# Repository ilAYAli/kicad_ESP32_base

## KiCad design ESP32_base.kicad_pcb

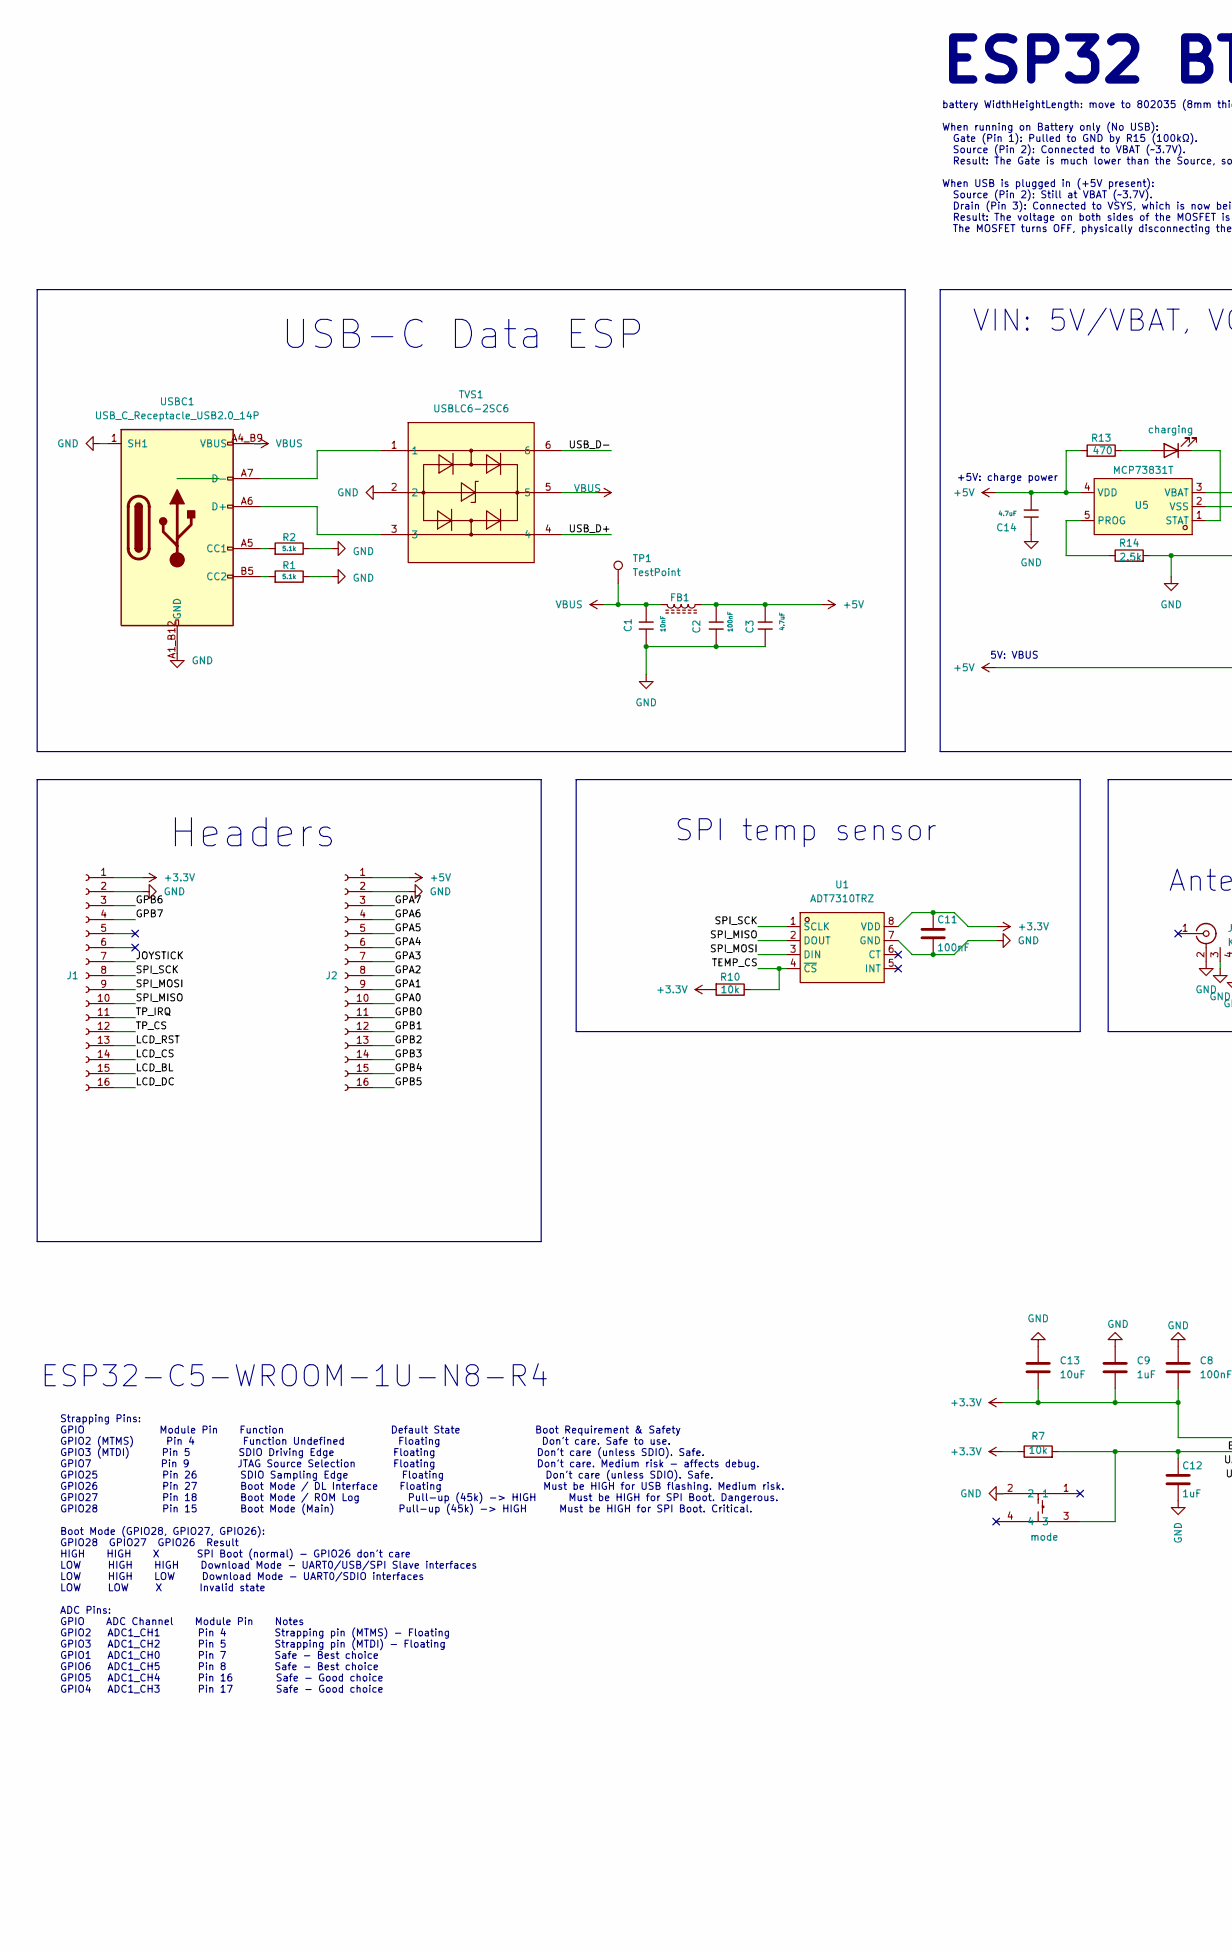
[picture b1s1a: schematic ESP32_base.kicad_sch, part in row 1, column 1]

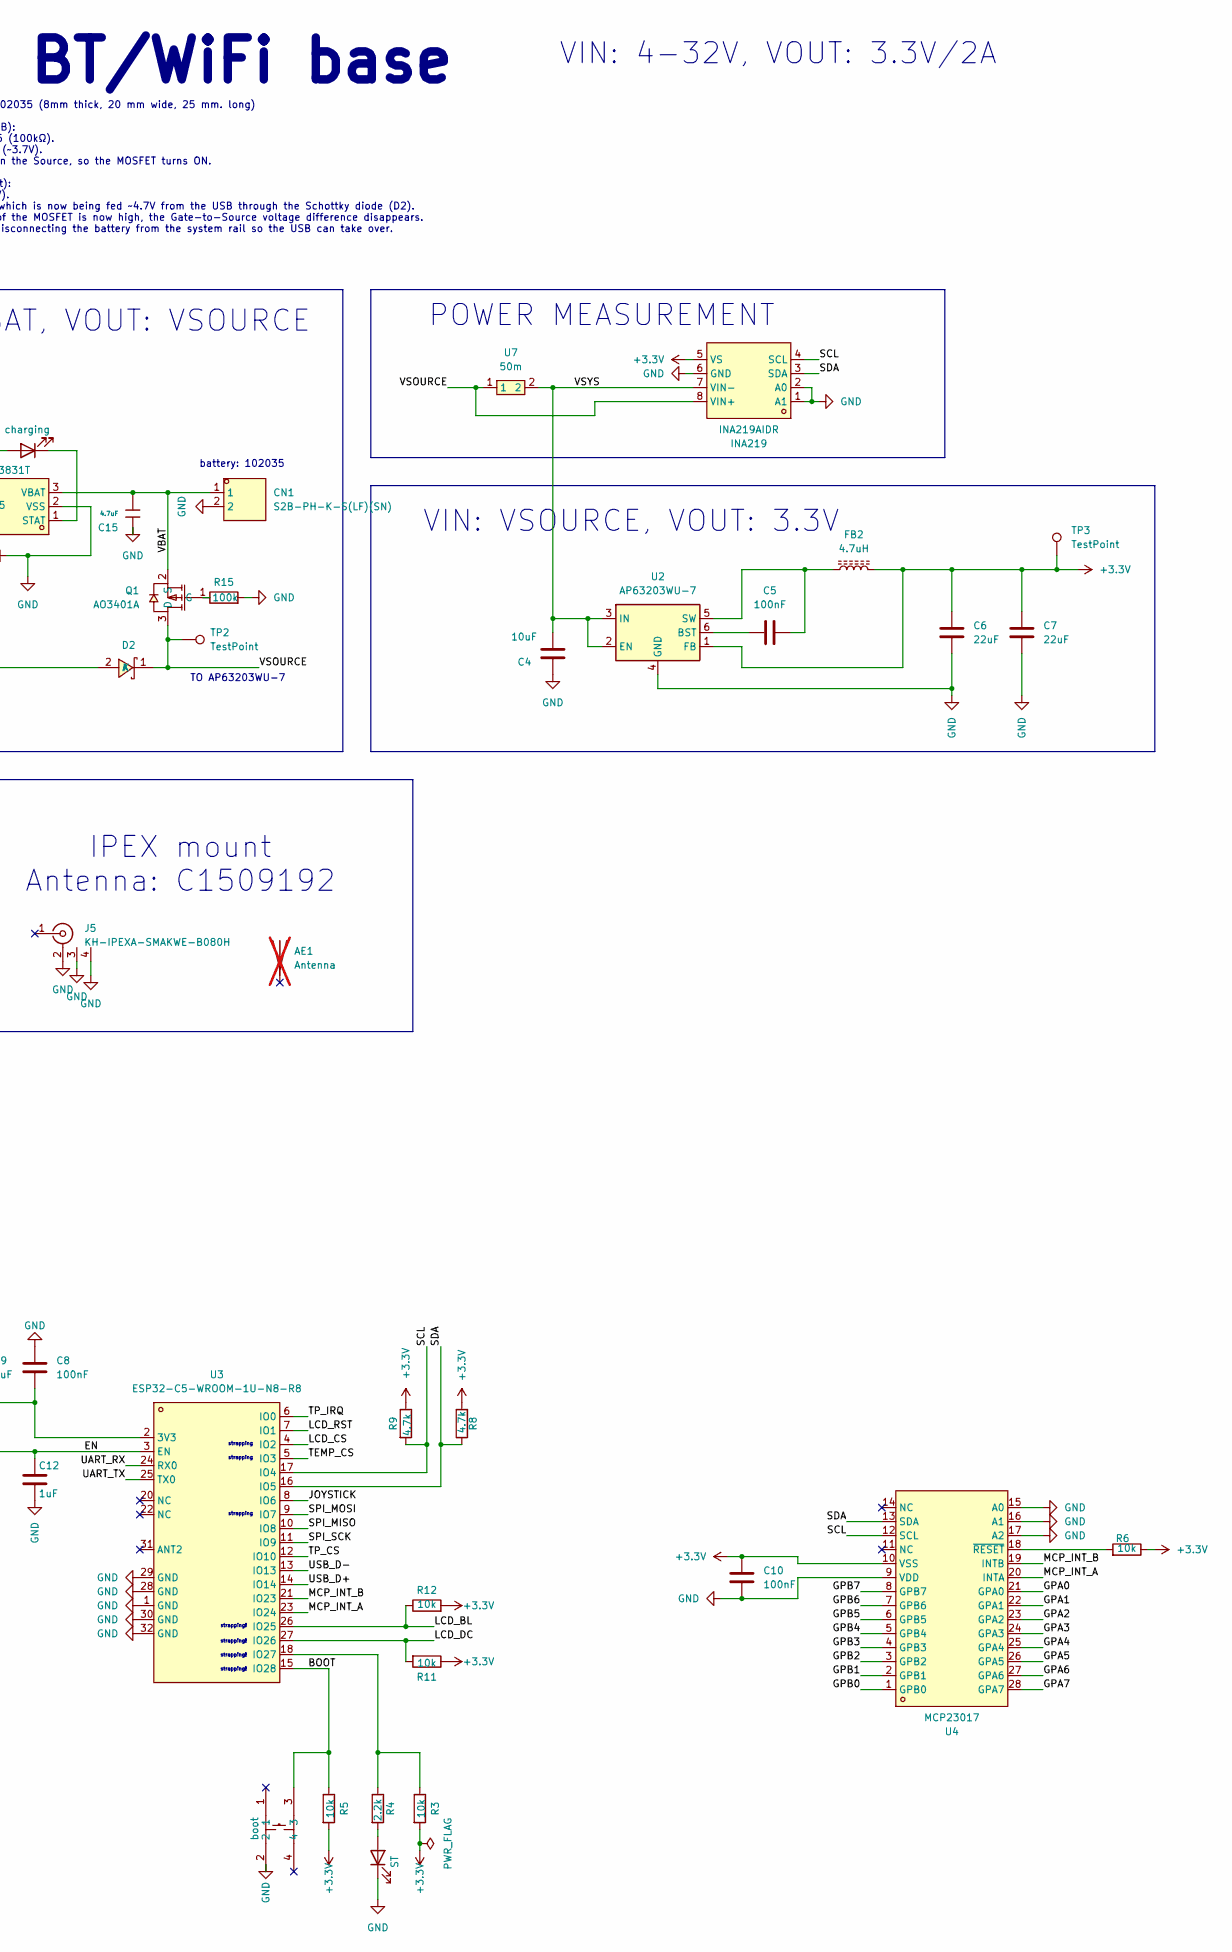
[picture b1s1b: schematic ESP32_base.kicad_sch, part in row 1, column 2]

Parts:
AE1: Antenna; LCSC Part C1509192; not fitted
C1: 10nF; C_0805_2012Metric; Mfr. Part CC0805KRX7R9BB103; LCSC Part C83170
C2, C5, C8, C10, C11: 100nF; C_0805_2012Metric; Mfr. Part CC0805KRX7R9BB104; LCSC Part C49678
C3: 4.7uF; C_0805_2012Metric; Mfr. Part GRM21BZ71H475KE15L; LCSC Part C437557
C4, C13: 10uF; C_0805_2012Metric; Mfr. Part GRM21BR61H106KE43L; LCSC Part C440198
C6, C7: 22uF; C_0805_2012Metric; Mfr. Part CGA0805X5R226M350MT; LCSC Part C6119901
C9, C12: 1uF; C_0805_2012Metric; Mfr. Part CL21B105KBFNNNE; LCSC Part C28323
C14, C15: 4.7uF; C_0805_2012Metric; Voltage Rated 25V; Tolerance ±10%; Part CL21A475KAQNNNE; LCSC C1779
CN1: S2B-PH-K-S(LF)(SN); CONN-TH_S2B-PH-K-S-LF-SN; LCSC Part C173752
D2: C426863; D_SOD-323; Mfr. Part PMEG1020EA,115; LCSC Part C146335
FB1: 600; L_0805_2012Metric; Mfr. Part MPZ2012S601AT000; LCSC Part C21519
FB2: 4.7uH; C_1210_3225Metric; Mfr. Part SRP3212A-4R7M
INA219: INA219AIDR; SOIC-8_L4.9-W3.9-P1.27-LS6.0-BL; LCSC Part C138706
J1: Conn_01x16_Socket; PinSocket_1x16_P2.54mm_Vertical; Mfr. Part KH-2.54FH-1X16P-H8.5; LCSC Part C19190305
J2: Conn_01x16_Socket; PinSocket_1x16_P2.54mm_Vertical; Mfr. Part KH-2.54FH-1X16P-H8.5; LCSC Part C2905421
J5: KH-IPEXA-SMAKWE-B080H; CONN-TH_KH-IPEX-SMAKWE; Mfr. Part KH-IPEXA-SMAKWE-B080H; LCSC Part C2919724
LED1: ST; LED_0805_2012Metric; Mfr. Part NCD0805G1; LCSC Part C84260
LED2: charging; LED_0805_2012Metric
Q1: AO3401A; SOT-23; LCSC Part C15127
R1, R2: 5.1k; R_0805_2012Metric; Mfr. Part 0805W8F5101T5E; LCSC Part C27834
R3, R5, R6, R7, R11, R12: 10k; R_0805_2012Metric; Mfr. Part RC0805FR-0710KL; LCSC Part C84376
R4: 2.2k; R_0805_2012Metric; Mfr. Part 0805W8F2201T5E; LCSC Part C17520
R8, R9: 4.7k; R_0805_2012Metric
R10: 10k; R_0805_2012Metric
R13: 470; R_0805_2012Metric
R14: 2.5k; R_0805_2012Metric
R15: 100k; R_0805_2012Metric
SW1: boot; SW-SMD_4P-L6.0-W6.0-P4.50-LS9.0-2; Mfr. Part TS-1002S-04526C; LCSC Part C455109
SW2: mode; SW-SMD_4P-L6.0-W6.0-P4.50-LS9.0-2; Mfr. Part TS-1002S-04526C; LCSC Part C455109
TP1, TP2, TP3: TestPoint; TestPoint_Pad_D1.0mm
TVS1: USBLC6-2SC6; SOT-23-6; Mfr. Part USBLC6-2SC6; LCSC Part C7519
U1: ADT7310TRZ; SOIC-8_L4.9-W3.9-P1.27-LS6.0-BL; Mfr. Part ADT7310TRZ; LCSC Part C660039
U2: AP63203WU-7; TSOT-23-6; Mfr. Part AP63203WU-7; LCSC Part C780769
U3: ESP32-C5-WROOM-1U-N8-R8; COMM-SMD_32P-L21.2-W18.0_ESP32-C5-WROOM-1U; Mfr. Part ESP32-C5-WROOM-1U-N8R4; LCSC Part C49308183
U4: MCP23017; SOIC-28_L18.0-W7.5-P1.27-LS10.3-BL; LCSC Part C47023
U5: MCP73831T; SOT-23-5_L3.0-W1.7-P0.95-LS2.8-BL; LCSC Part C424093
U7: 50m; R1206; Mfr. Part FRM121WFR050TM; LCSC Part C7467249
USBC1: USB_C_Receptacle_USB2.0_14P; USB-C_Receptacle

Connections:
+3.3V: C6.2, C7.2, C8.2, C9.2, C10.1, C11.1, C13.1, FB2.2, INA219.5 (VS), J1.1, R3.2, R5.2, R6.1, R7.1, R8.2, R9.1, R10.2, R11.1, R12.2, TP3.1, U1.8 (VDD), U2.1 (FB), U3.2 (3V3), U4.10 (VSS)
+5V: C2.1, C3.1, C14.1, D2.2 (A), FB1.1, J2.1, R13.2, U5.4 (VDD)
/BOOT: R5.1, SW1.3, U3.15 (IO28)
/EN: C12.1, R7.2, SW2.3, U3.3 (EN)
/GPA0: J2.10, U4.21 (GPA0)
/GPA1: J2.9, U4.22 (GPA1)
/GPA2: J2.8, U4.23 (GPA2)
/GPA3: J2.7, U4.24 (GPA3)
/GPA4: J2.6, U4.25 (GPA4)
/GPA5: J2.5, U4.26 (GPA5)
/GPA6: J2.4, U4.27 (GPA6)
/GPA7: J2.3, U4.28 (GPA7)
/GPB0: J2.11, U4.1 (GPB0)
/GPB1: J2.12, U4.2 (GPB1)
/GPB2: J2.13, U4.3 (GPB2)
/GPB3: J2.14, U4.4 (GPB3)
/GPB4: J2.15, U4.5 (GPB4)
/GPB5: J2.16, U4.6 (GPB5)
/GPB6: J1.3, U4.7 (GPB6)
/GPB7: J1.4, U4.8 (GPB7)
/JOYSTICK: J1.7, U3.8 (IO6)
/LCD_BL: J1.15, R12.1, U3.26 (IO25)
/LCD_CS: J1.14, U3.4 (IO2)
/LCD_DC: J1.16, R11.2, U3.27 (IO26)
/LCD_RST: J1.13, U3.7 (IO1)
/MCP_INT_A: U3.23 (IO24), U4.20 (INTA)
/MCP_INT_B: U3.21 (IO23), U4.19 (INTB)
/SCL: INA219.4 (SCL), R9.2, U3.17 (IO4), U4.12 (SCL)
/SDA: INA219.3 (SDA), R8.1, U3.16 (IO5), U4.13 (SDA)
/SPI_MISO: J1.10, U1.2 (DOUT), U3.10 (IO8)
/SPI_MOSI: J1.9, U1.3 (DIN), U3.9 (IO7)
/SPI_SCK: J1.8, U1.1 (SCLK), U3.11 (IO9)
/TEMP_CS: R10.1, U1.4 (~CS), U3.5 (IO3)
/TP_CS: J1.12, U3.12 (IO10)
/TP_IRQ: J1.11, U3.6 (IO0)
/UART_RX: U3.24 (RX0)
/UART_TX: U3.25 (TX0)
/USB_D+: TVS1.4, U3.14 (IO14)
/USB_D-: TVS1.6, U3.13 (IO13)
/VBAT: C15.1, CN1.1, Q1.2 (S), U5.3 (VBAT)
/VSOURCE: D2.1 (K), INA219.8 (VIN+), Q1.3 (D), TP2.1, U7.1
/VSYS: C4.1, INA219.7 (VIN-), U2.2 (EN), U2.3 (IN), U7.2
GND: C1.2, C2.2, C3.2, C4.2, C6.1, C7.1, C8.1, C9.1, C10.2, C11.2, C12.2, C13.2, C14.2, C15.2, CN1.2, INA219.1 (A1), INA219.2 (A0), INA219.6 (GND), J1.2, J2.2, J5.2 (Ext), J5.3 (Ext), J5.4 (Ext), LED1.1 (K), R1.2, R2.2, R14.2, R15.2, SW1.2, SW2.2, TVS1.2, U1.7 (GND), U2.4 (GND), U3.1 (GND), U3.28 (GND), U3.29 (GND), U3.30 (GND), U3.32 (GND), U4.9 (VDD), U4.15 (A0), U4.16 (A1), U4.17 (A2), U5.2 (VSS), USBC1.1 (SH1), USBC1.2 (SH2), USBC1.3 (SH3), USBC1.4 (SH4), USBC1.A1_B12 (GND), USBC1.B1_A12 (GND)
unnamed: LED1.2 (A), R4.2
unnamed: LED2.2 (A), R13.1
unnamed: LED2.1 (K), U5.1 (STAT)
unnamed: Q1.1 (G), R15.1
unnamed: TVS1.1, USBC1.A7 (D-), USBC1.B7 (D-)
unnamed: TVS1.3, USBC1.A6 (D+), USBC1.B6 (D+)
unnamed: C5.2, U2.6 (BST)
unnamed: C5.1, FB2.1, U2.5 (SW)
unnamed: R3.1, R4.1, U3.18 (IO27)
unnamed: R6.2, U4.18 (~RESET)
unnamed: R14.1, U5.5 (PROG)
unnamed: R2.1, USBC1.A5 (CC1)
unnamed: R1.1, USBC1.B5 (CC2)
VBUS: C1.1, FB1.2, TP1.1, TVS1.5, USBC1.A4_B9 (VBUS), USBC1.B4_A9 (VBUS)

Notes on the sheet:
ESP32 BT/WiFi base
strapping
ESP32-C5-WROOM-1U-N8-R4
IPEX mount Antenna: C1509192
strapping!
USB-C Data ESP
VIN: 5V/VBAT, VOUT: VSOURCE
+5V: charge power
TO AP63203WU-7
battery WidthHeightLength: move to 802035 (8mm thick, 20 mm wide, 25 mm. long) When running on Battery only (No USB): Gate (Pin 1): Pulled to GND by R15 (100kΩ). Source (Pin 2): Connected to VBAT (~3.7V). Result: The Gate is much lower than the Source, so the MOSFET turns ON. When USB is plugged in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
5V: VBUS
VIN: VSOURCE, VOUT: 3.3V
VIN: 4-32V, VOUT: 3.3V/2A
Headers
SPI temp sensor
battery: 102035
Strapping Pins: GPIO Module Pin Function Default State Boot Requirement & Safety GPIO2 (MTMS) Pin 4 Function Undefined Floating Don't care. Safe to use. GPIO3 (MTDI) Pin 5 SDIO Driving Edge Floating Don't care (unless SDIO). Safe. GPIO7 Pin 9 JTAG Source Selection Floating Don't care. Medium risk -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
POWER MEASUREMENT

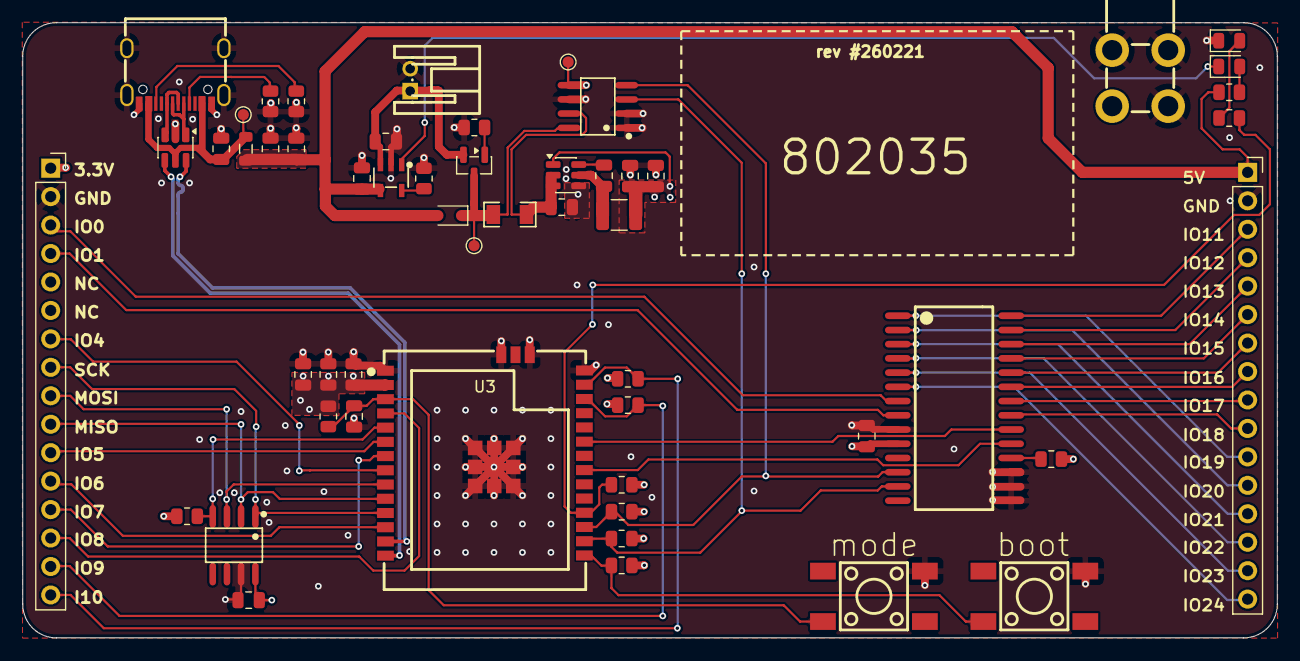
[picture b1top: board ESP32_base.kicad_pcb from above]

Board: 4 copper layers, 112.0 x 54.9 mm, 54 parts (0 on the bottom side), 55 nets.

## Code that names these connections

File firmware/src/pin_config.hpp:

#pragma once
#include <cstdint>
// ESP32 Pin Assignments
enum class Pin : uint8_t {
    // SPI Shared Bus (SPI2)
    ADT_CLK     = 0,   // Pin 6 (GPIO0)
    ADT_MOSI    = 1,   // Pin 7 (GPIO1)
    ADT_MISO    = 8,   // Pin 10 (GPIO8)
    // ADT7310 Temperature Sensor
    ADT_CS      = 23,  // Pin 21 (GPIO23)
    // LCD (HS280S010B)
    LCD_CS      = 25,  // Pin 26 (GPIO25)
    LCD_RST     = 11,  // Pin 25 (GPIO11/TX0)
    LCD_DC      = 10,  // Pin 12 (GPIO10)
    LCD_BCKL    = 26,  // Pin 27 (GPIO26)
    // Touchpad
    TP_CS       = 12,  // Pin 12 (U0RXD, GPIO12)
    TP_IRQ      = 24,  // Pin 23 (GPIO24)
    // Input devices
    JOYSTICK    = 3,   // Pin 5 (IO3/ADC1_CH2)
    BOOT        = 28   // Pin 15 (GPIO28)
};

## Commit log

2025-11-24 initial
2026-01-04 fix power lines, DRC, ...
2026-01-04 USB differential pair routing
2026-01-05 pre re-rouring PSRAM
2026-01-05 production ready
2026-01-06 pre move temp sensor
2026-01-06 multi route
2026-01-07 fixed signal width at 0.3mm
2026-01-07 production ready #2
2026-01-08 production ready: 26.01.08
2026-01-09 replace power circuit
2026-01-10 0805
2026-01-11 pre spreading signals
2026-01-11 increase signal clearance
2026-01-11 route EN across MCU
2026-01-11 cleanup lower left corner
2026-01-12 1206 -> 0805 and no ERC errors
2026-01-13 new USBC header
2026-01-13 update PWA lib
2026-01-13 sync lib
2026-01-13 remove easyEDA TVS sym
2026-01-13 LCSP -> LCSC
2026-01-13 Part -> Mfr. Part
2026-01-13 header: remove BOM spam
2026-01-13 remve SPI BOM spam
2026-01-13 BOM cleanup
2026-01-13 remove BOM buck
2026-01-13 IPEX remove BOM spam
2026-01-13 remove BOM spam
2026-01-13 BOM spam
2026-01-13 production_13_01_26
2026-01-14 BOM: fix 01x16 connector
2026-01-16 sync
2026-01-24 MCP: re-route and reallocate pins. Additionally, define ADC pins
2026-01-25 update USBC connector model
2026-01-25 fix USBC connector
2026-01-25 add MCU vias
2026-01-25 trivial
2026-01-26 update hash
2026-01-27 WIP: return path
2026-01-28 major fuckup: pin 13/14 (USB D+/D-) swapped
2026-01-29 fix spokes and zone clearance
2026-01-30 show cap values etc.
2026-02-01 move to 4 layer board
2026-02-03 no DRC 4 layers
2026-02-03 fix buck feedback
2026-02-03 add 3v3 buck copper zone
2026-02-04 update IPEX connector ground and descriptions
2026-02-04 use new USB-C connector
2026-02-05 wip: battery
2026-02-06 wip: pre solid pads
2026-02-08 production_260208
2026-02-17 wip: INA219
2026-02-17 add ESP32_ files
2026-02-17 add firmware as part of base repo
2026-02-17 LCD: fix orientation for red LCD
2026-02-17 Add IRQ-driven touch handling and wake-up timing
2026-02-17 Reduce graph flicker with incremental rendering
2026-02-17 Improve touch controller filtering with median sampling and coordinate jump detection
    - Replace mean averaging with median filtering (9 samples) to reject outliers naturally
    - Add IQR and range-based spread detection to reject very noisy readings
    - Implement raw coordinate jump detection: reject touches within 200ms with >800 unit difference
    - Increase ISR debounce to 30ms for better tap responsiveness
    - Remove application-level proximity filtering that was blocking legitimate touches
    - Simplify duplicate detection to hardware-level only
2026-02-20 routing improbements: diff pair, vias
2026-02-21 angle via traces
2026-02-21 update library
2026-02-21 possibly broken 3dmodels
2026-02-23 button: reset -> mode
2026-02-25 thinner signal traces
2026-03-15 use new battery connector
